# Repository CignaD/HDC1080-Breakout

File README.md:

This is a small brakout board (10mm x 10mm) for use with the TI HDC1080 humidity and temperature sensor

There are pads on both sides of the board for a 100n ceramic capacitor, but only one needs to be populated depending on how the board is mounted.

Electrical connection is by four PTH on 0.05" centers. This makes it convenient to solder ordinary ribbon cable on either side of the board.

There are four mounting holes, 1mm in from each corner which allows heat staking to a 3D printed enclosure.

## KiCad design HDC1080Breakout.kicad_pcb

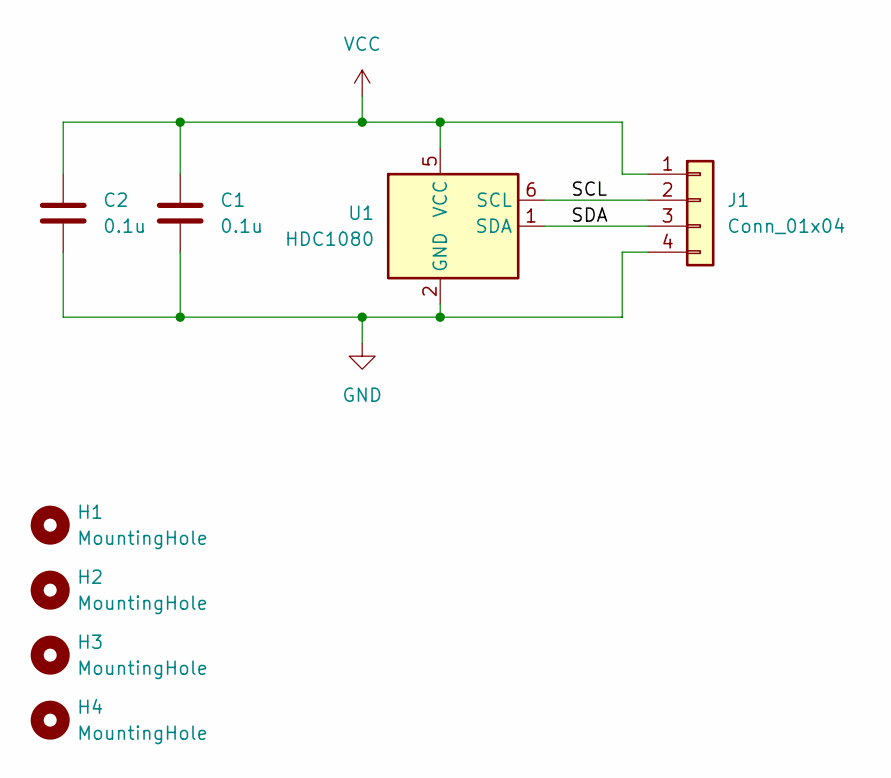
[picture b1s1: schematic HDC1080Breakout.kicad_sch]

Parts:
C1, C2: 0.1u; C_0603_1608Metric
H1, H2, H3, H4: MountingHole; MountingHole-1mm
J1: Conn_01x04; PinHeader_1x04_P1.27mm_Vertical
U1: HDC1080; Texas_PWSON-N6

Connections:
/SCL: J1.2, U1.6 (SCL)
/SDA: J1.3, U1.1 (SDA)
GND: C1.2, C2.2, J1.4, U1.2 (GND)
VCC: C1.1, C2.1, J1.1, U1.5 (VCC)

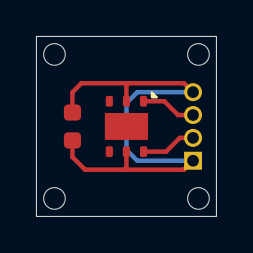
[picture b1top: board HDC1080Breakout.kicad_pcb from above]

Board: 2 copper layers, 10.0 x 10.0 mm, 8 parts (1 on the bottom side), 4 nets.

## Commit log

2026-03-10 Add files via upload
    Initial commit
2026-03-10 Update silk
2026-03-11 updated silk
